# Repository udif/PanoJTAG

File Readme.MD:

This is a KiCAD design (5.99 based) for a voltage level translator that can fit inside the PanoLogic G2. It is intended to develop a cheap JTAG probe by handling the voltage conversion part.
A TX0104B-based design was considered, but abandoned since it has many problems:
* Cannot use in any designs with pullups or pulldowns below 50K
* Max JTAG pin capacitance must be 70pF (which is probably OK, but you need to check that)

Instead, the sn74avc4t774pw was chosen because it used acive drivers with individual direction pins.
The only limitation is that the maximum voltage it can drive is 3.6v which is OK for us.

Note that J3 is optional and only used for debugging the JTAG programmer itself.

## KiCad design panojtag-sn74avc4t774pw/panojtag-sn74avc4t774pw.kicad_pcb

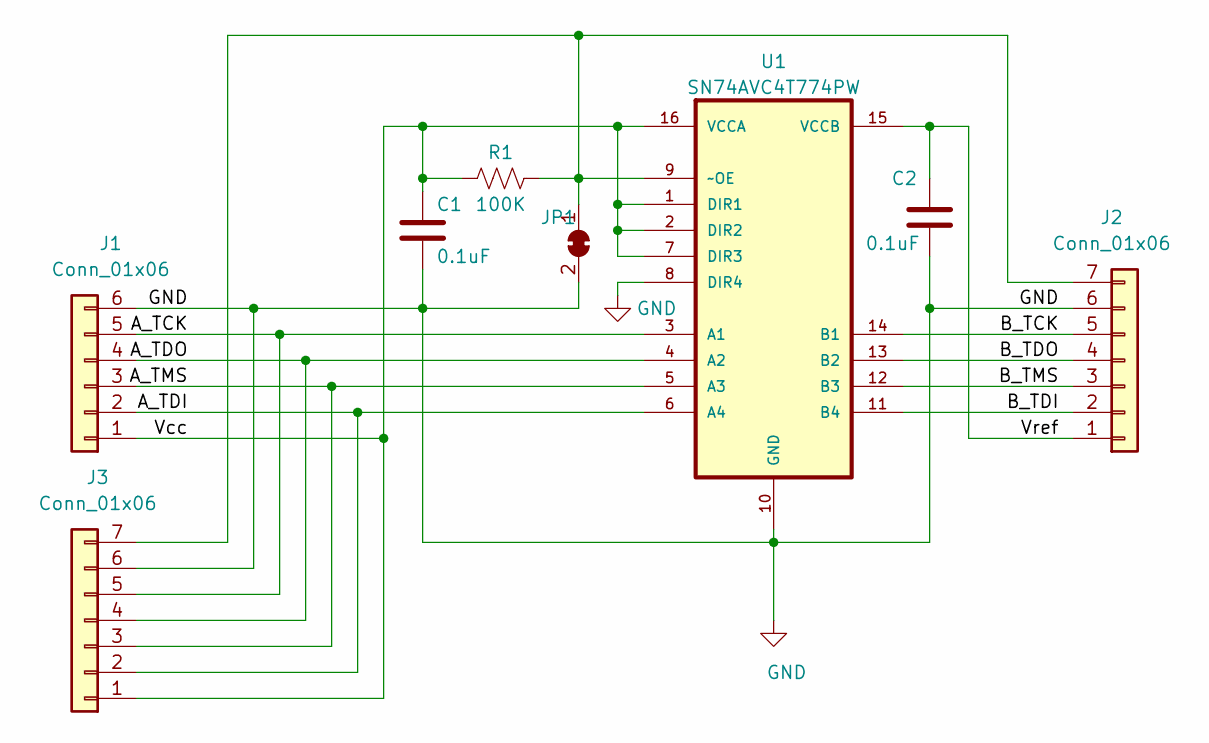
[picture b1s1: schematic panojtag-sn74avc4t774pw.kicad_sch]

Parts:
C1, C2: 0.1uF; C_0805_2012Metric
J1: Conn_01x06; PinSocket_1x06_P1.27mm_Vertical
J2, J3: Conn_01x06; PinHeader_1x07_P2.54mm_Vertical
JP1: SolderJumper_2_Bridged; SolderJumper-2_P1.3mm_Bridged_Pad1.0x1.5mm
R1: 100K; R_0805_2012Metric_Pad1.20x1.40mm_HandSolder
U1: SN74AVC4T774PW; SOP65P640X120-16N

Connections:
/A_TCK: J1.5, J3.5, U1.3 (A1)
/A_TDI: J1.2, J3.2, U1.6 (A4)
/A_TDO: J1.4, J3.4, U1.4 (A2)
/A_TMS: J1.3, J3.3, U1.5 (A3)
/B_TCK: J2.5, U1.14 (B1)
/B_TDI: J2.2, U1.11 (B4)
/B_TDO: J2.4, U1.13 (B2)
/B_TMS: J2.3, U1.12 (B3)
/Vcc: C1.1, J1.1, J3.1, R1.1, U1.1 (DIR1), U1.2 (DIR2), U1.7 (DIR3), U1.16 (VCCA)
/Vref: C2.1, J2.1, U1.15 (VCCB)
GND: C1.2, C2.2, J1.6, J2.6, J3.6, JP1.2 (B), U1.8 (DIR4), U1.10 (GND)
unnamed: J2.7, J3.7, JP1.1 (A), R1.2, U1.9 (~OE)

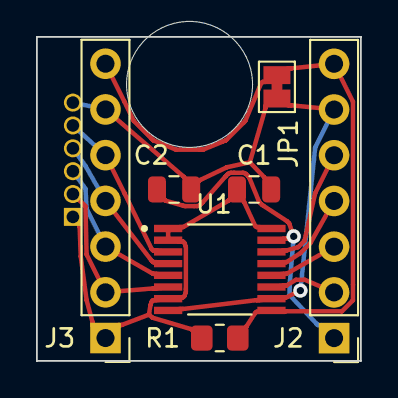
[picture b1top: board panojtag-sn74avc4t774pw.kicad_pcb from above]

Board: 2 copper layers, 18.0 x 18.0 mm, 8 parts (1 on the bottom side), 12 nets.

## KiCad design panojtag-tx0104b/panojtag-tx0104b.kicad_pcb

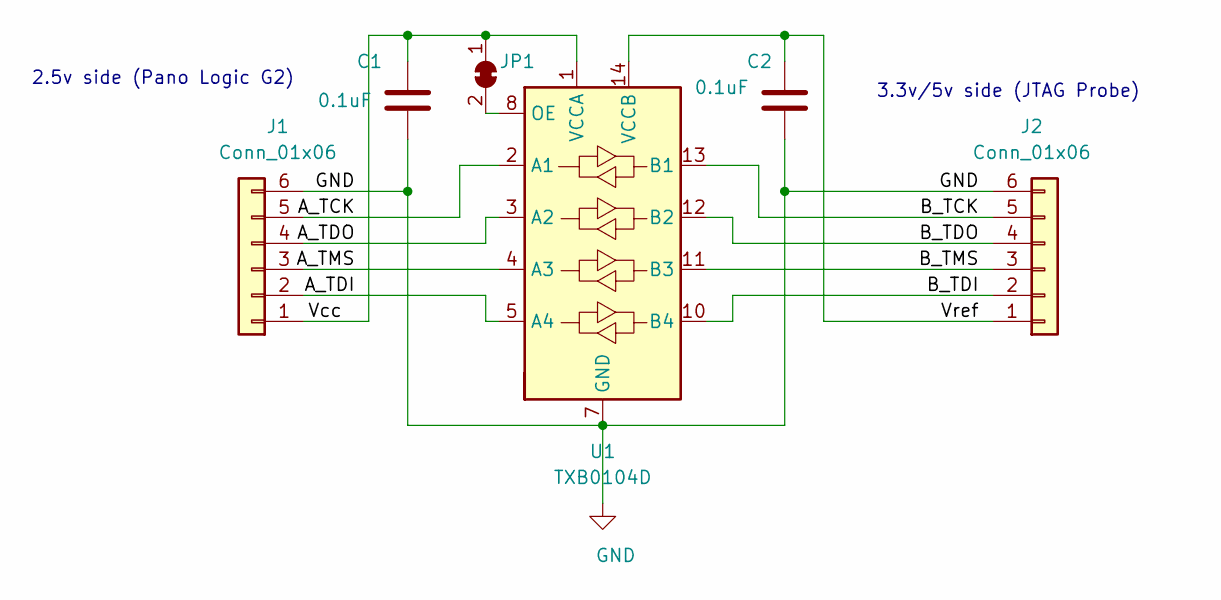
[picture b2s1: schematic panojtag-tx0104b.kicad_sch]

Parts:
C1, C2: 0.1uF; C_0805_2012Metric
J1: Conn_01x06; PinHeader_1x06_P1.27mm_Vertical
J2: Conn_01x06; PinHeader_1x06_P2.54mm_Vertical
JP1: SolderJumper_2_Bridged; SolderJumper-2_P1.3mm_Bridged_Pad1.0x1.5mm
U1: TXB0104D; SOIC-14_3.9x8.7mm_P1.27mm

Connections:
/A_TCK: J1.5, U1.2 (A1)
/A_TDI: J1.2, U1.5 (A4)
/A_TDO: J1.4, U1.3 (A2)
/A_TMS: J1.3, U1.4 (A3)
/B_TCK: J2.5, U1.13 (B1)
/B_TDI: J2.2, U1.10 (B4)
/B_TDO: J2.4, U1.12 (B2)
/B_TMS: J2.3, U1.11 (B3)
/Vcc: C1.1, J1.1, JP1.1 (A), U1.1 (VCCA)
/Vref: C2.1, J2.1, U1.14 (VCCB)
GND: C1.2, C2.2, J1.6, J2.6, U1.7 (GND)
unnamed: JP1.2 (B), U1.8 (OE)

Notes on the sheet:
2.5v side (Pano Logic G2)
3.3v/5v side (JTAG Probe)

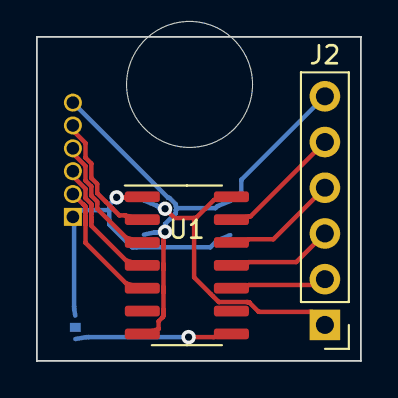
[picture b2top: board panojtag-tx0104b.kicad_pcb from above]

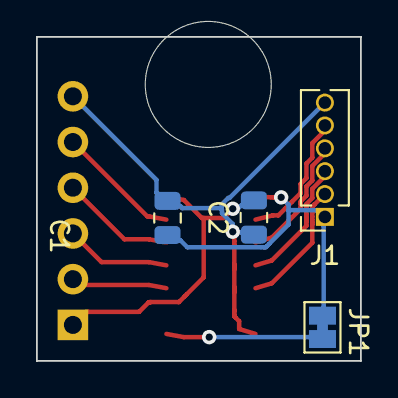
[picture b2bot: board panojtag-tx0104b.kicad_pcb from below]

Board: 2 copper layers, 18.0 x 18.0 mm, 6 parts (4 on the bottom side), 12 nets.

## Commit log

2021-07-08 Initial version based on TX0104B
2021-07-08 renamed files before changing design
2021-07-08 Moved TX0104B to its own subdir.
2021-07-08 Cleaned up and routed TX0104B version, but e're not going to use it. Routed using TopoR with 45deg tracks.
2021-07-09 Initial commit for sn74avc4t774pw based design Added another 100mil connector for JTAG debugging Added 7th pin for optional driver /OE control.
2021-07-09 Added a README file.
2021-07-09 Fixed newline
2021-07-09 Added 3D render.
2021-07-09 Fixes
2021-07-09 More README fixes
